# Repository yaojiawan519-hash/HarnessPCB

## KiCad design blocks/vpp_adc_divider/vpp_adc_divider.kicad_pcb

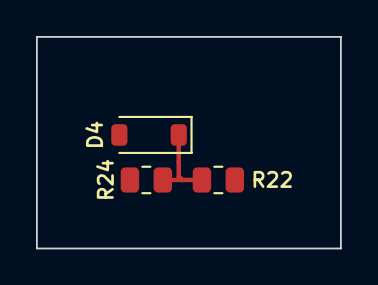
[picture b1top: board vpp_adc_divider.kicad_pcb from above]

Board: 2 copper layers, 16.9 x 11.8 mm, 3 parts (0 on the bottom side), 2 nets.

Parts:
D4: 4.7V; D_SOD-123
R22: 10K; R_0805_2012Metric
R24: 2K; R_0805_2012Metric

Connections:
GND: D4.2 (A), R24.2
VPP_ADC: D4.1 (K), R22.2, R24.1

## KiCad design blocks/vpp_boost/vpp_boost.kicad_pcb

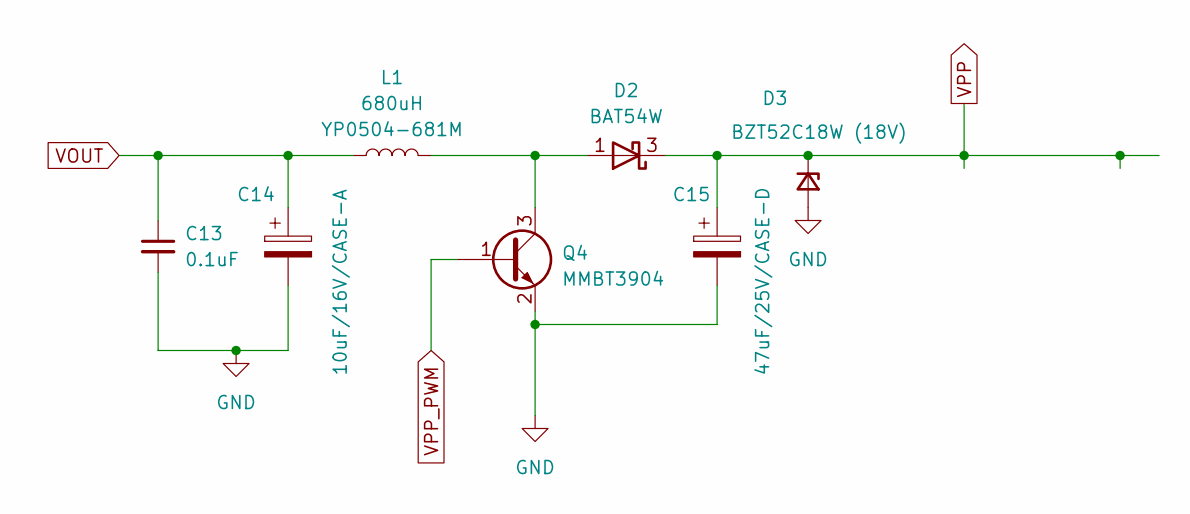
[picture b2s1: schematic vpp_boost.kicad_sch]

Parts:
C13: 0.1uF; C_0805_2012Metric_Pad1.18x1.45mm_HandSolder
C14: 10uF/16V/CASE-A; CP_EIA-3216-18_Kemet-A
C15: 47uF/25V/CASE-D; CP_EIA-7343-31_Kemet-D
D2: BAT54W; SOT-23
D3: BZT52C18W (18V); D_SOD-123
L1: 680uH; L_YP0504; MPN YP0504-681M
Q4: MMBT3904; SOT-23

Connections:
GND: C13.2, C14.2, C15.2, D3.2 (A), Q4.2 (E)
unnamed: D2.1 (A), L1.2, Q4.3 (C)
VOUT: C13.1, C14.1, L1.1
VPP: C15.1, D2.3 (K), D3.1 (K)
VPP_PWM: Q4.1 (B)

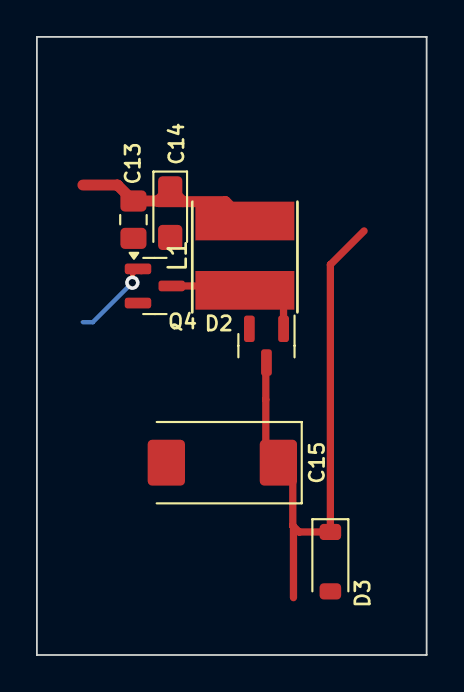
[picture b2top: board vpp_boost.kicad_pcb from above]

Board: 2 copper layers, 21.7 x 34.3 mm, 7 parts (0 on the bottom side), 4 nets.

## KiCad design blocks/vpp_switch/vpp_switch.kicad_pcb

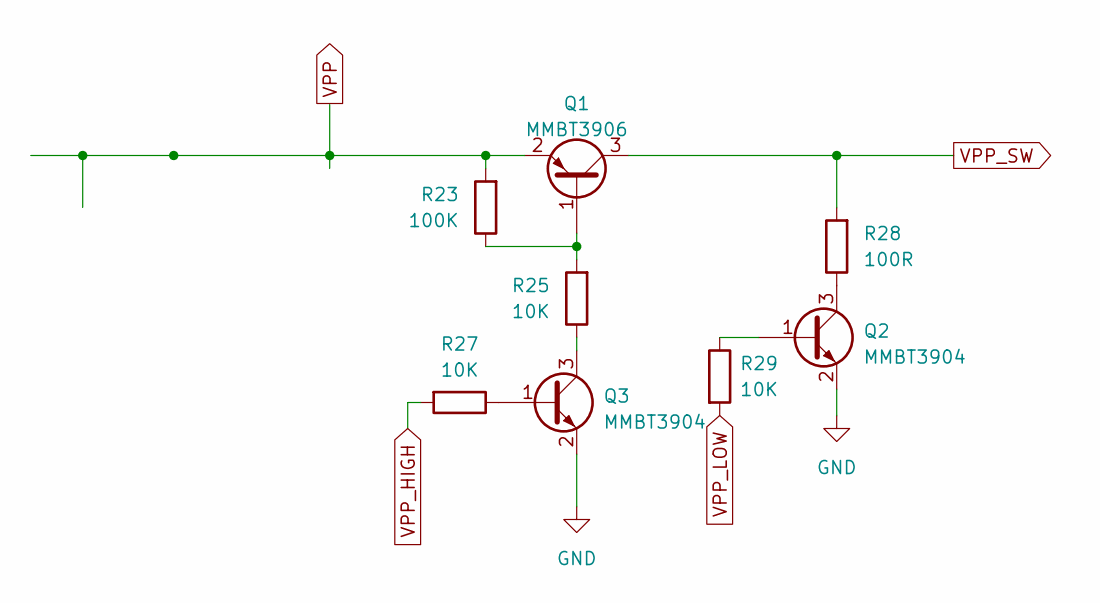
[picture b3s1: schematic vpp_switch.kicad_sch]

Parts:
Q1: MMBT3906; SOT-23
Q2, Q3: MMBT3904; SOT-23
R23: 100K; R_0805_2012Metric
R25, R27, R29: 10K; R_0805_2012Metric
R28: 100R; R_0805_2012Metric

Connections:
GND: Q2.2 (E), Q3.2 (E)
unnamed: Q1.1 (B), R23.1, R25.2
unnamed: Q2.1 (B), R29.1
unnamed: Q2.3 (C), R28.1
unnamed: Q3.1 (B), R27.1
unnamed: Q3.3 (C), R25.1
VPP: Q1.2 (E), R23.2
VPP_HIGH: R27.2
VPP_LOW: R29.2
VPP_SW: Q1.3 (C), R28.2

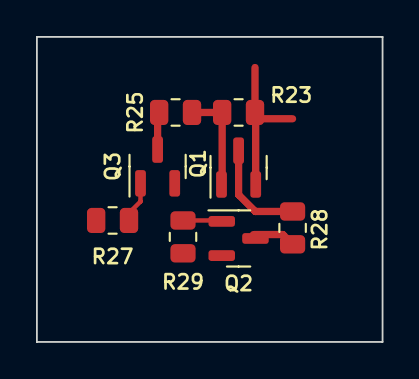
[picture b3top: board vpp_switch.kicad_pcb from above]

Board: 2 copper layers, 19.2 x 16.9 mm, 8 parts (0 on the bottom side), 8 nets.

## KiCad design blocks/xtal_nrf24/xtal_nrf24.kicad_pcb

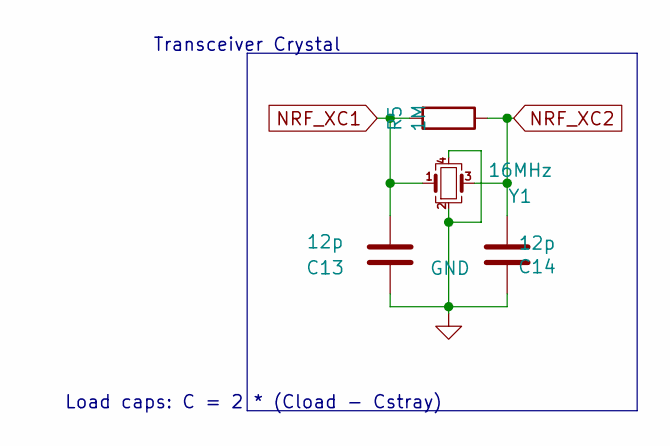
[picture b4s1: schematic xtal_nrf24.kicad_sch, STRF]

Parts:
C13, C14: 12p; C_0402_1005Metric
R5: 1M; R_0402_1005Metric
Y1: 16MHz; Crystal_SMD_3225-4Pin_3.2x2.5mm

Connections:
GND: C13.2, C14.2, Y1.2, Y1.4
NRF_XC1: C13.1, R5.2, Y1.1
NRF_XC2: C14.1, R5.1, Y1.3

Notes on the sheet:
Load caps: C = 2 * (Cload - Cstray)
Transceiver Crystal

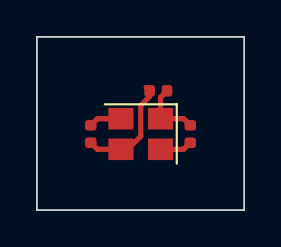
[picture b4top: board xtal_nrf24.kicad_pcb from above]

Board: 2 copper layers, 11.5 x 9.6 mm, 4 parts (0 on the bottom side), 3 nets.
